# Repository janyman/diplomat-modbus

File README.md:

# Modbus for Thermia Diplomat geothermal heat pumps

This project implements a Modbus RTU slave interface to Thermia heat pumps. The firmware is written in plain C for an AVR microcontroller.

The author has a Thermia Diplomat Optimum heatpump manufactured in the year 2020. This software could work with other Thermia or Danfoss heat pumps of the same era, but there is no guarantee for that.

## Disclamer 

This software and schematics in this repository should be considered an experimental project, and is published just as a reference in case somebody finds it interesting. There is no guarantee that anything in this repository is suitable for any kind of use. You should never open the covers of the heat pump unless you know what you are doing and understand the risks. You must always ensure that the device is disconnected from the electrical supply.

## What exists currently

A firmware implementation that polls a number of Control unit registers, and makes the values accessible via Modbus. There is no support for changing value of registers via Modbus. There are several reliability issues howeer.

The firmware is being developed on an Arduino Uno board, ATmega328P microcontroller. There is a Modbus RTU interface implementation, but there is no RS485 transciever support yet. 

* Modbus RTU slave address 10
* 9600 bps, 8E1 (build with `BAUD=19200` for 19200 bps)

### Custom ATmega328P board clock and fuses

The Arduino Uno uses a 16 MHz external crystal. The custom board has no
crystal, so build it for the ATmega328P's calibrated 8 MHz internal RC
oscillator:

```sh
make clean all BAUD=9600
```

The low fuse must select the internal oscillator and leave `CKDIV8`
unprogrammed. The recommended low fuse is `0xE2`; leaving the factory
`CKDIV8` setting in place would run the chip at 1 MHz and make 9600/19200
UART operation inaccurate. At 8 MHz, the normal UART divisor gives about
0.16% baud error at both 9600 and 19200 bps.

Program the fuses over ISP before or after flashing the application:

```sh
make read-fuses PROGRAMMER=usbasp PROGRAMMER_PORT=
make fuses PROGRAMMER=usbasp PROGRAMMER_PORT=
make flash PROGRAMMER=usbasp PROGRAMMER_PORT=
```

The default fuse set (`LFUSE=0xE2`, `HFUSE=0xD9`, `EFUSE=0xFF`) is for a bare
application without a bootloader. If a bootloader is installed, use its
required high/extended fuse values, but retain `LFUSE=0xE2` for the internal
8 MHz clock. Fuse writes can make a device inaccessible when the selected
clock source or programmer wiring is wrong; use ISP and verify with
`make read-fuses`.

Factory settings:
-`LFUSE=0x62`: internal 8 MHz RC oscillator divided by 8 → actual CPU clock is 1 MHz
- `HFUSE=0xD9`: suitable for direct ISP application startup
- `EFUSE=0xFF`: brown-out detection disabled

Modbus poll command:

```sh
mbpoll -a 10 -b 9600 -P even -t 3 -r 1000 -c 20  /dev/ttyACM0
```

## Background information: The Ext.COM bus

Careful examination of the Thermia Diplomat wiring diagram shows that the Control unit (451) has an interface called "Ext. COM". This is the only official reference of what appears to be an I2C bus, as explained in the Finnish-language article ["Danfoss-lämpöpumpun salaisuudet"](https://omakotikotitalomme.blogspot.com/2015/03/danfoss-lampopumpun-salaisuudet.html). 

### Physical layer

The Ext.COM bus connector is labelled "EXT" on the Control unit board inside the heat pump enclosure. The connector is a 4-way pin header with 2.54 mm pitch.

)

Measurements on a 2020 Thermia Diplomat Optimum show the EXT bus as I2C with 5V signal levels and operating at 400 kHz serial clock rate. The pin assignment is the following, starting from the topmost pin:

1. +5V Vcc supply rail?
2. SCL
3. SDA
4. GND

### Can we use the +5V rail of Ext.COM bus to power something?

I haven't been able to find any information about the +5V rail on the connector.

I have made some empirical measurements, and I believe it is possible to draw some tens of mA continously from the +5V pin, but *we don't have any official specification* about this.

My tests suggest the following:

    * Unloaded voltage: about 4.975 V, which is coherent with rail being a proper 5 V supply.
    * ~10.6 mA load (470 Ω): essentially no significant voltage drop, just a fiew 10 mV.
    * ~22.7 mA load (220 Ω): the rail remains close to 5 V.
    * ~50 mA load (100 Ω): the rail still settles around 4.9 V.

So it seems that the +5V pin of Ext.COM behaves like a fairly stiff +5V rail, at the current levels needed for a MCU+RS485 hardware, estimated at around 20 mA. The fall in voltage as current increases could be due to some kind of protection element present on the rail, but we don't know. It certainly appears that the rail is not directly fed from a voltage regulator, as it isn't as low-impedance as one would expect from an output of a dedicated regulator.

### I2C bus details

In the I2C bus, the heat pump is the bus master. A quick explanation of the bus follows: The master periodically polls certain I2C addresses on the bus by sending a poll byte, and the slaves respond with a request byte or a place-holder value. 

The bus master polls for expansion card at address 0x2e, but they say that also other expansion cards at other addresses are polled for. However, I have never witnessed any other i2c slave being addressed, besides 0x2e. It also appears that third-party commercial products (ThermIQ, which I have no experience with) also implement an i2c interface with same slave address 0x2e.

If the slave responds with the place-holder value, then nothing special happens, and the bus master sends an other poll soon after. But if the slave responds with a request byte, then the bus master sends the data corresponding to the request byte with in a subsequent bus write transaction.

In practice, the bus works like this: the master addresses slave 0x2e in a write transaction containing one byte 0xfe, which can be understood as the master asking the slave if there is something the slave wants to do. 

The slave has the possibility to reply with one byte. The byte can either have special value 0xff, which probably is just an acknowledgement of slave presence, and in that case the master does nothing more, it just sends an other probe after a short while. 

But if the slave responds with a byte other than 0xff, then that byte value is understood to be the address a of data register whose value the slave wants to know. In that case, the bus master starts an other I2C write transaction addressing the slave, and sends three bytes: the requested register address, and the low and high bytes of the 16-bit register value. 

### I2C implementation notes

The current implementation does the protocol processing inside callbacks called from the i2c (twi) interrupt routine - this is OK for now, but we must be extra careful that we don't start spending too much time inside the isr, as that causes the MCU to hold SCL low during that time (in other words, we would introduce clock stretching) and we don't know if the Ext.COM bus master supports that.

## Hardware

The connector SV1 is for I2C

1. VCC +5V
2. SCL
3. SDA
4. GND

## References

EXT bus secrets revealed: https://omakotikotitalomme.blogspot.com/2015/03/danfoss-lampopumpun-salaisuudet.html
Registers: https://thermiq.net/ThermIQ_MQTT_Installation.pdf

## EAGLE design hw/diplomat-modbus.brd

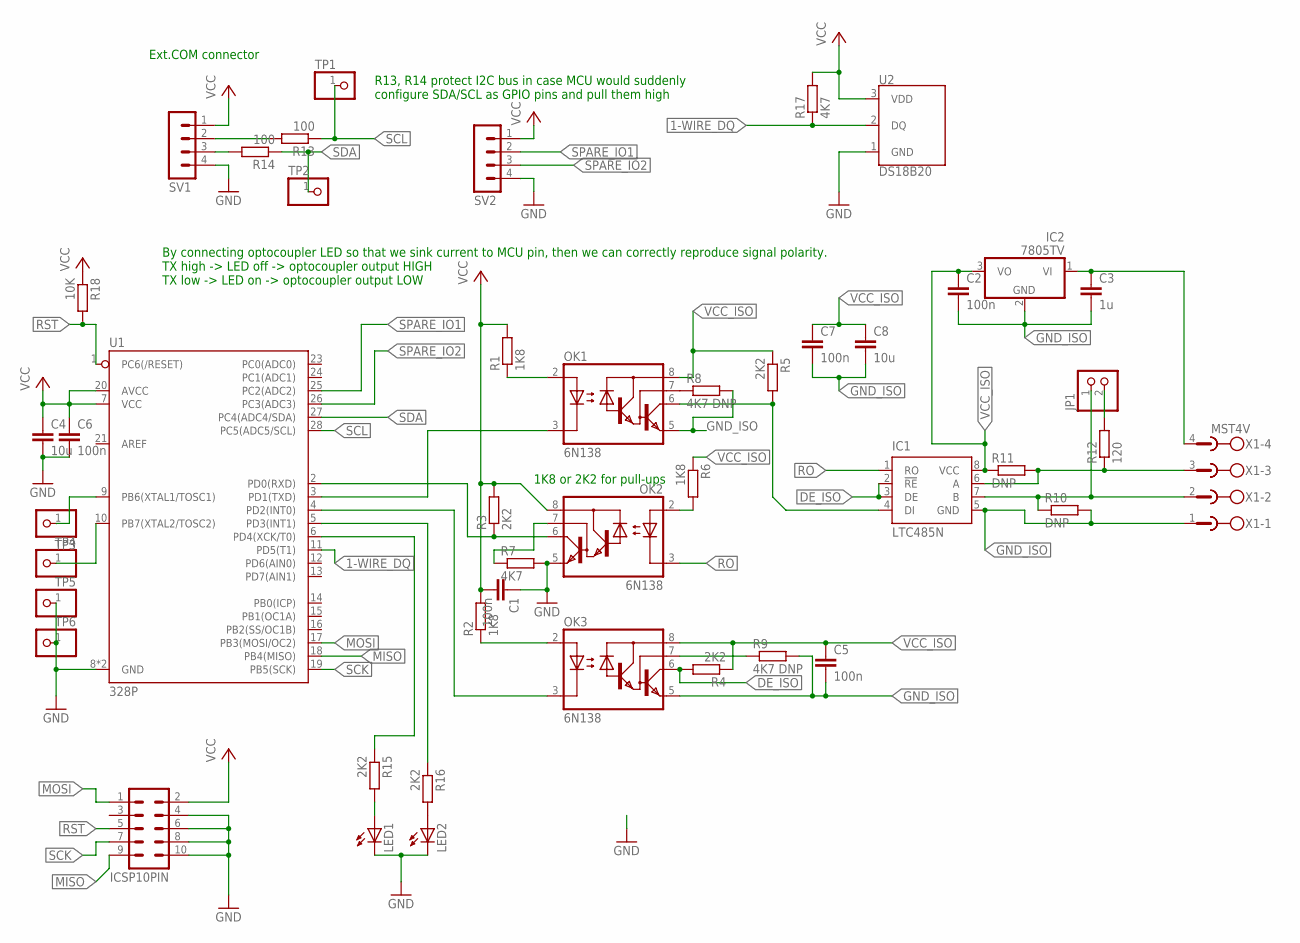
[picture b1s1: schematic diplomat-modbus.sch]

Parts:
C1, C2, C5, C6, C7: 100n; C025-024X044
C3: 1u; C025-024X044
C4, C8: 10u; C025-024X044
IC1: LTC485N; DIL08
IC2: 7805TV; TO220V
ICSP10PIN: MA05-2
JP1: PINHD-1X2; 1X02
LED1, LED2: LED3MM
OK1, OK2, OK3: 6N138; DIL08
R1, R2, R6: 1K8; 0309V
R3, R4, R5, R15, R16: 2K2; 0309V
R7, R17: 4K7; 0309V
R8, R9: 4K7 DNP; 0309V
R10, R11: DNP; 0309V
R12: 120; 0309V
R13, R14: 100; 0309V
R18: 10K; 0309V
SV1, SV2: MA04-1
TP1, TP2, TP3, TP4, TP5, TP6: PINHD-1X1; 1X01
U1: 328P; DIP28
U2: DS18B20; TO-92-AMMO
X1: MST4V; MSTBV4

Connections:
1-WIRE_DQ: R17.1, U1.11 (PD5(T1)), U2.2 (DQ)
DE_ISO: IC1.2 (!RE), IC1.3 (DE), OK3.6 (VO), R4.2
GND: C1.1, C4.2, C6.2, ICSP10PIN.4, ICSP10PIN.6, ICSP10PIN.8, ICSP10PIN.10, LED1.K (C), LED2.K (C), OK2.5 (GND), R7.2, SV1.4, SV2.4, TP5.1, TP6.1, U1.8 (GND), U1.22 (GND), U2.1 (GND)
GND_ISO: C2.2, C3.2, C5.2, C7.2, C8.2, IC1.5 (GND), IC2.2 (GND), OK1.5 (GND), OK3.5 (GND), R8.2, R9.2, R10.2, X1.1
MISO: ICSP10PIN.9, U1.18 (PB4(MISO))
MOSI: ICSP10PIN.1, U1.17 (PB3(MOSI/OC2))
unnamed: OK1.3 (C), U1.3 (PD1(TXD))
unnamed: OK1.2 (A), R1.1
unnamed: OK3.2 (A), R2.1
unnamed: OK3.3 (C), U1.4 (PD2(INT0))
unnamed: JP1.2, R12.2
unnamed: IC1.4 (DI), OK1.6 (VO), R5.2
unnamed: TP3.1, U1.9 (PB6(XTAL1/TOSC1))
unnamed: OK2.2 (A), R6.2
unnamed: IC1.7 (B), JP1.1, R10.1, X1.2
unnamed: IC1.6 (A), R11.2, R12.1, X1.3
unnamed: C3.1, IC2.1 (VI), X1.4
unnamed: OK2.7 (VB), R7.1
unnamed: OK1.7 (VB), R8.1
unnamed: R13.2, SV1.2
unnamed: OK3.7 (VB), R9.1
unnamed: R15.1, U1.6 (PD4(XCK/T0))
unnamed: R16.1, U1.5 (PD3(INT1))
unnamed: LED1.A, R15.2
unnamed: LED2.A, R16.2
unnamed: TP4.1, U1.10 (PB7(XTAL2/TOSC2))
RO: IC1.1 (RO), OK2.3 (C)
RST: ICSP10PIN.5, R18.2, U1.1 (PC6(/RESET))
RX: OK2.6 (VO), R3.1, U1.2 (PD0(RXD))
SCK: ICSP10PIN.7, U1.19 (PB5(SCK))
SCL: R13.1, TP1.1, U1.28 (PC5(ADC5/SCL))
SDA: R14.1, TP2.1, U1.27 (PC4(ADC4/SDA))
SPARE_IO1: SV2.2, U1.25 (PC2(ADC2))
SPARE_IO2: SV2.3, U1.26 (PC3(ADC3))
VCC: C1.2, C4.1, C6.1, ICSP10PIN.2, OK2.8 (VCC), R1.2, R2.2, R3.2, R17.2, R18.1, SV1.1, SV2.1, U1.7 (VCC), U1.20 (AVCC), U2.3 (VDD)
VCC_ISO: C2.1, C5.1, C7.1, C8.1, IC1.8 (VCC), IC2.3 (VO), OK1.8 (VCC), OK3.8 (VCC), R4.1, R5.1, R6.1, R11.1
XXX: R14.2, SV1.3

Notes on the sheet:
By connecting optocoupler LED so that we sink current to MCU pin, then we can correctly reproduce signal polarity. TX high -> LED off -> optocoupler output HIGH TX low -> LED on -> optocoupler output LOW
1K8 or 2K2 for pull-ups
Ext.COM connector
R13, R14 protect I2C bus in case MCU would suddenly configure SDA/SCL as GPIO pins and pull them high

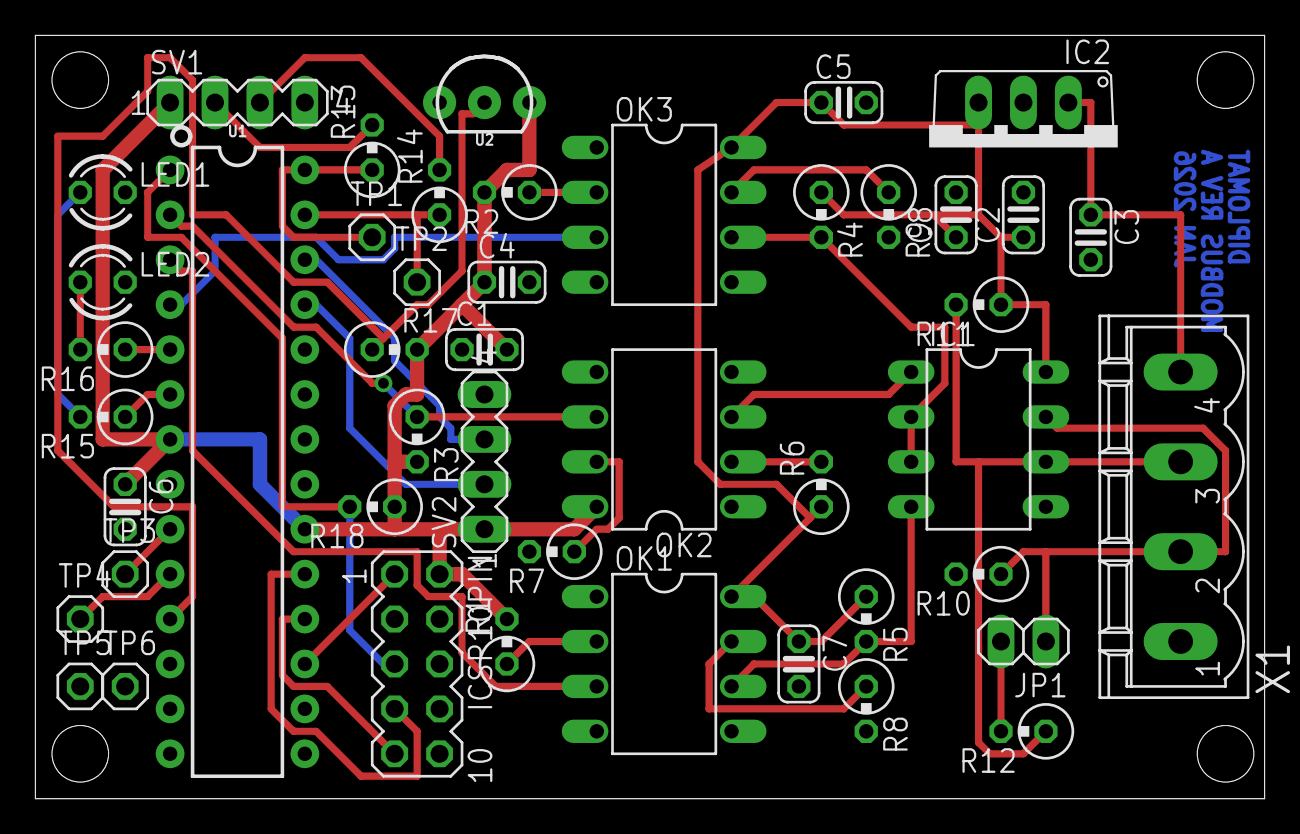
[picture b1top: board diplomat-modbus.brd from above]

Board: 2 copper layers, 69.5 x 43.2 mm, 46 parts (0 on the bottom side), 37 nets.

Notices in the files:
parts and their libraries:
SparkFun-IC-Microcontroller: Licensing: Creative Commons ShareAlike 4.0 International - https://creativecommons.org/licenses/by-sa/4.0
